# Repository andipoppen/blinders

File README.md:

# BLE controlled and motorized window blind

This project is a based on a [motorized window blind](https://www.instructables.com/id/Motorized-WiFi-IKEA-Roller-Blind/) that is using the IKEA Tupplur blind. 

The difference from the original is that this project uses BLE to control the window blind and the BLE module is built in the motor holder.

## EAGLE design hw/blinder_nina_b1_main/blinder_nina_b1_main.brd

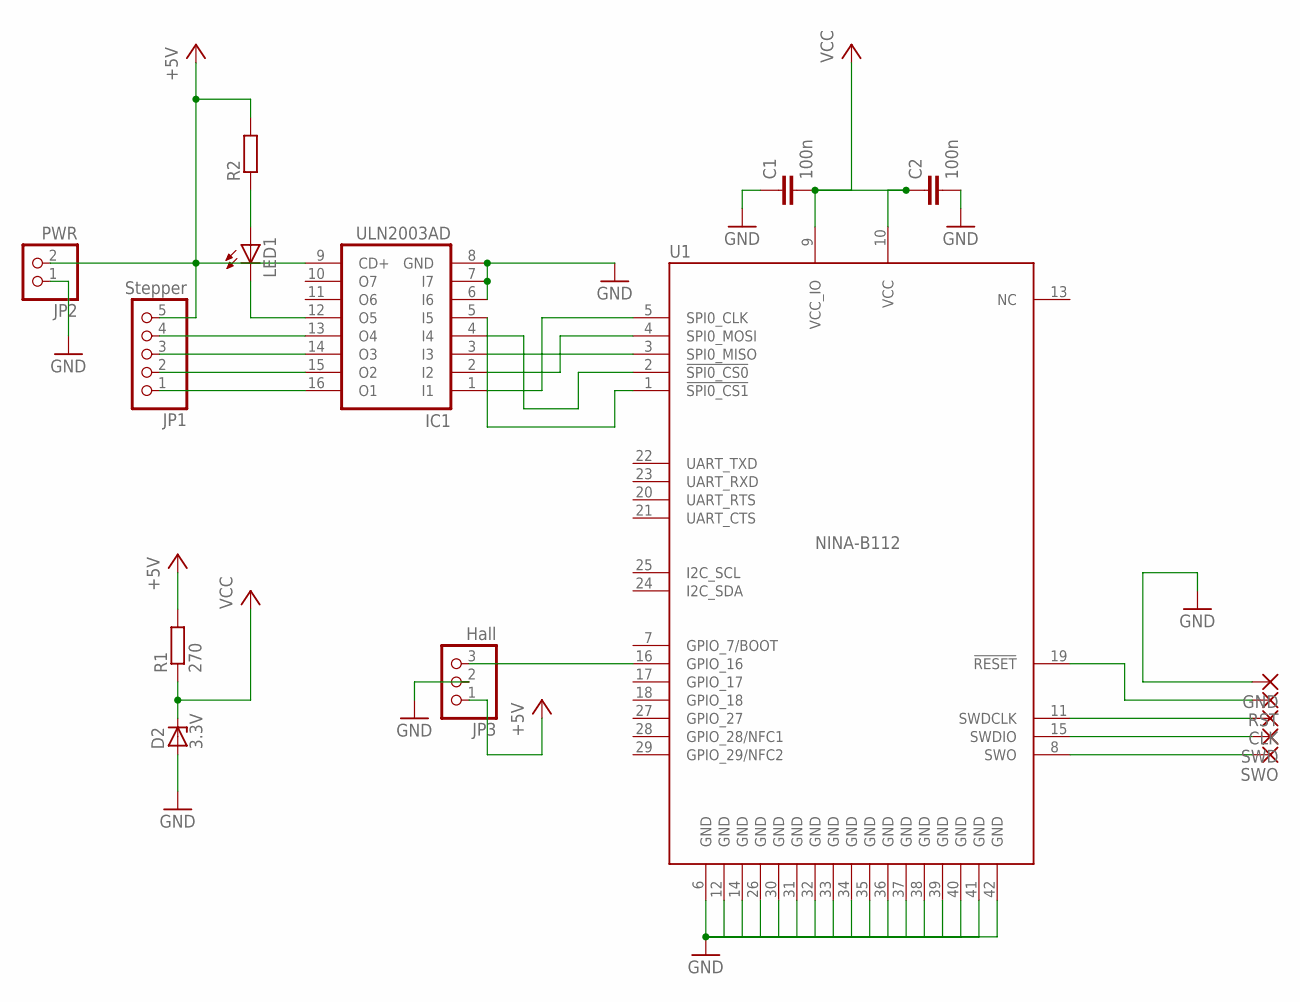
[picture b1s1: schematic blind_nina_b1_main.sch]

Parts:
C1, C2: 100n; C0603
CLK: SMD2; SMD1,27-2,54
D2: 3.3V; SOD80C
GND: SMD2; SMD1,27-2,54
IC1: ULN2003AD; SO16
JP1: Stepper; 1X05
JP2: PWR; 1X02
JP3: Hall; 1X03
LED1: LED_E; LED_1206
R1: 270; R1210W
R2: R-EU_R0603; R0603
RST: SMD2; SMD1,27-2,54
SWD: SMD2; SMD1,27-2,54
SWO: SMD2; SMD1,27-2,54
U1: NINA-B112; NINA112-42

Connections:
+5V: IC1.9 (CD+), JP1.5, JP2.2, JP3.1, R1.2, R2.2
GND: C1.1, C2.2, D2.A, GND.1, IC1.6 (I6), IC1.7 (I7), IC1.8 (GND), JP2.1, JP3.2, U1.6 (GND), U1.12 (GND), U1.14 (GND), U1.26 (GND), U1.30 (GND), U1.31 (GND), U1.32 (GND), U1.33 (GND), U1.34 (GND), U1.35 (GND), U1.36 (GND), U1.37 (GND), U1.38 (GND), U1.39 (GND), U1.40 (GND), U1.41 (GND), U1.42 (GND)
unnamed: IC1.1 (I1), U1.5 (SPI0_CLK)
unnamed: IC1.2 (I2), U1.4 (SPI0_MOSI)
unnamed: IC1.3 (I3), U1.3 (SPI0_MISO)
unnamed: IC1.4 (I4), U1.2 (!SPI0_CS0)
unnamed: SWO.1, U1.8 (SWO)
unnamed: IC1.16 (O1), JP1.1
unnamed: IC1.15 (O2), JP1.2
unnamed: IC1.14 (O3), JP1.3
unnamed: IC1.13 (O4), JP1.4
unnamed: SWD.1, U1.15 (SWDIO)
unnamed: CLK.1, U1.11 (SWDCLK)
unnamed: RST.1, U1.19 (!RESET)
unnamed: IC1.12 (O5), LED1.C
unnamed: JP3.3, U1.16 (GPIO_16)
unnamed: LED1.A, R2.1
unnamed: IC1.5 (I5), U1.1 (!SPI0_CS1!)
VCC: C1.2, C2.1, D2.C, R1.1, U1.9 (VCC_IO), U1.10 (VCC)

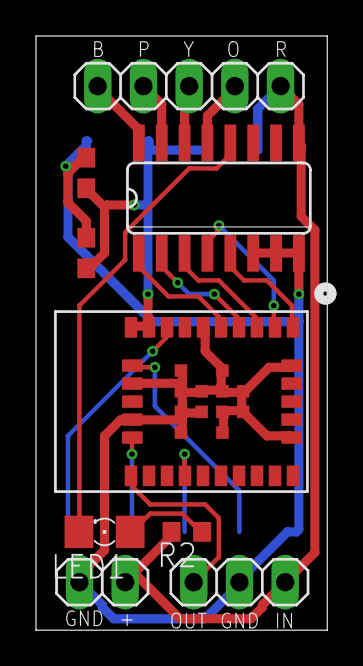
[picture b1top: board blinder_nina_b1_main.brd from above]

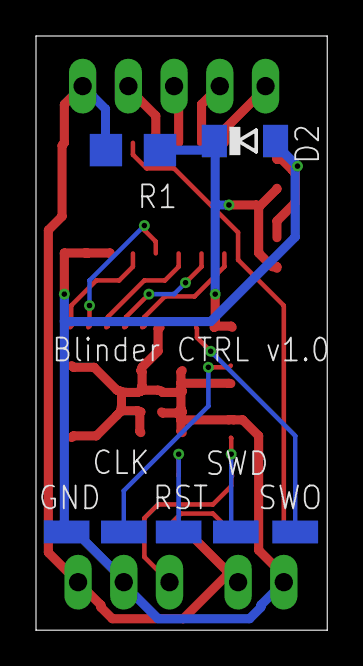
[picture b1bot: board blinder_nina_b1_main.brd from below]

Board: 2 copper layers, 16.2 x 33.0 mm, 16 parts (7 on the bottom side), 19 nets.

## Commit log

2017-04-22 Added
2017-04-26 Fixed nicer and bigger cutouts. Fixed better naming of cuts
2018-10-19 Added first version of SW
2018-10-24 Updated mount_base
2018-10-24 Renamed blinder -> blind
2018-11-08 Fixed name clash for ble. Uncommented DataStorage.
